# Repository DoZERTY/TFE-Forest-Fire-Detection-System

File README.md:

# ForestFireDetection
This repository contains the work and source files associated with the Master's thesis of Dorian Schrobiltgen. The project builds upon the previous work conducted in [ForestMEv2-public](https://forge.uclouvain.be/nbrusselmans/forestmev2-public).

## Objective

The aim of this thesis is to design and evaluate a low-power, wireless sensor node capable of detecting the early signs of forest fires. The system combines gas sensing, RF communication and optimized embedded hardware/software to ensure early and reliable detection in forest environments, while minimizing the environmental impact of each end-node.

## Project Structure
The repository is devided into four main parts:
### Hardware
- **new_prototype/**: Contains PCB designs, schematics, and Bill of Material (BoM) for the new hardware prototype.
- **test_antenna/**: Designs and schematics related to PCBs used for antenna impedance testing.

### Measurements
- **Gas_sensor/**: Includes raw data, analysis script and plots related to $CO_2$ concentration profile testing.

- **Power_consumption/**: Detailed power consumption for the initial and new prototype.

- **RF_network/**: Results from RF performance tests performed using the antenna impedance testing PCBs

### Simulations
- **Analysis/**: A collection of Python scripts for power consumption modeling, supercapacitor sizing, and generation of plots used in the thesis report.
- **FWI/**: Contains the optimized C implementation of the Fire Weather Index (FWI), along with a repository (by Reid Sawtell in [pyFWI](https://github.com/buckinha/pyfwi)) used for validation.
- **LCA/**: Life Cycle Assessment files used to quantify the environmental impact of each end-node.

### Software
This directory contains the full STM32 projects used to program the boards. Each folder includes all necessary files to build, flash, and debug the corresponding prototype using **STM32CubeIDE**.
- **initial_prototype/**: Complete project and source code of the optimized software for the initial hardware prototype.
- **new_prototype/**: Complete project and source code of the optimized software for the new hardware prototype.

## Author
Dorian Schrobiltgen is an Electrical Engineering student, specializing in Electronics and Power Systems (UCLouvain).

E-mail : dorian.schrobilgen@gmail.com

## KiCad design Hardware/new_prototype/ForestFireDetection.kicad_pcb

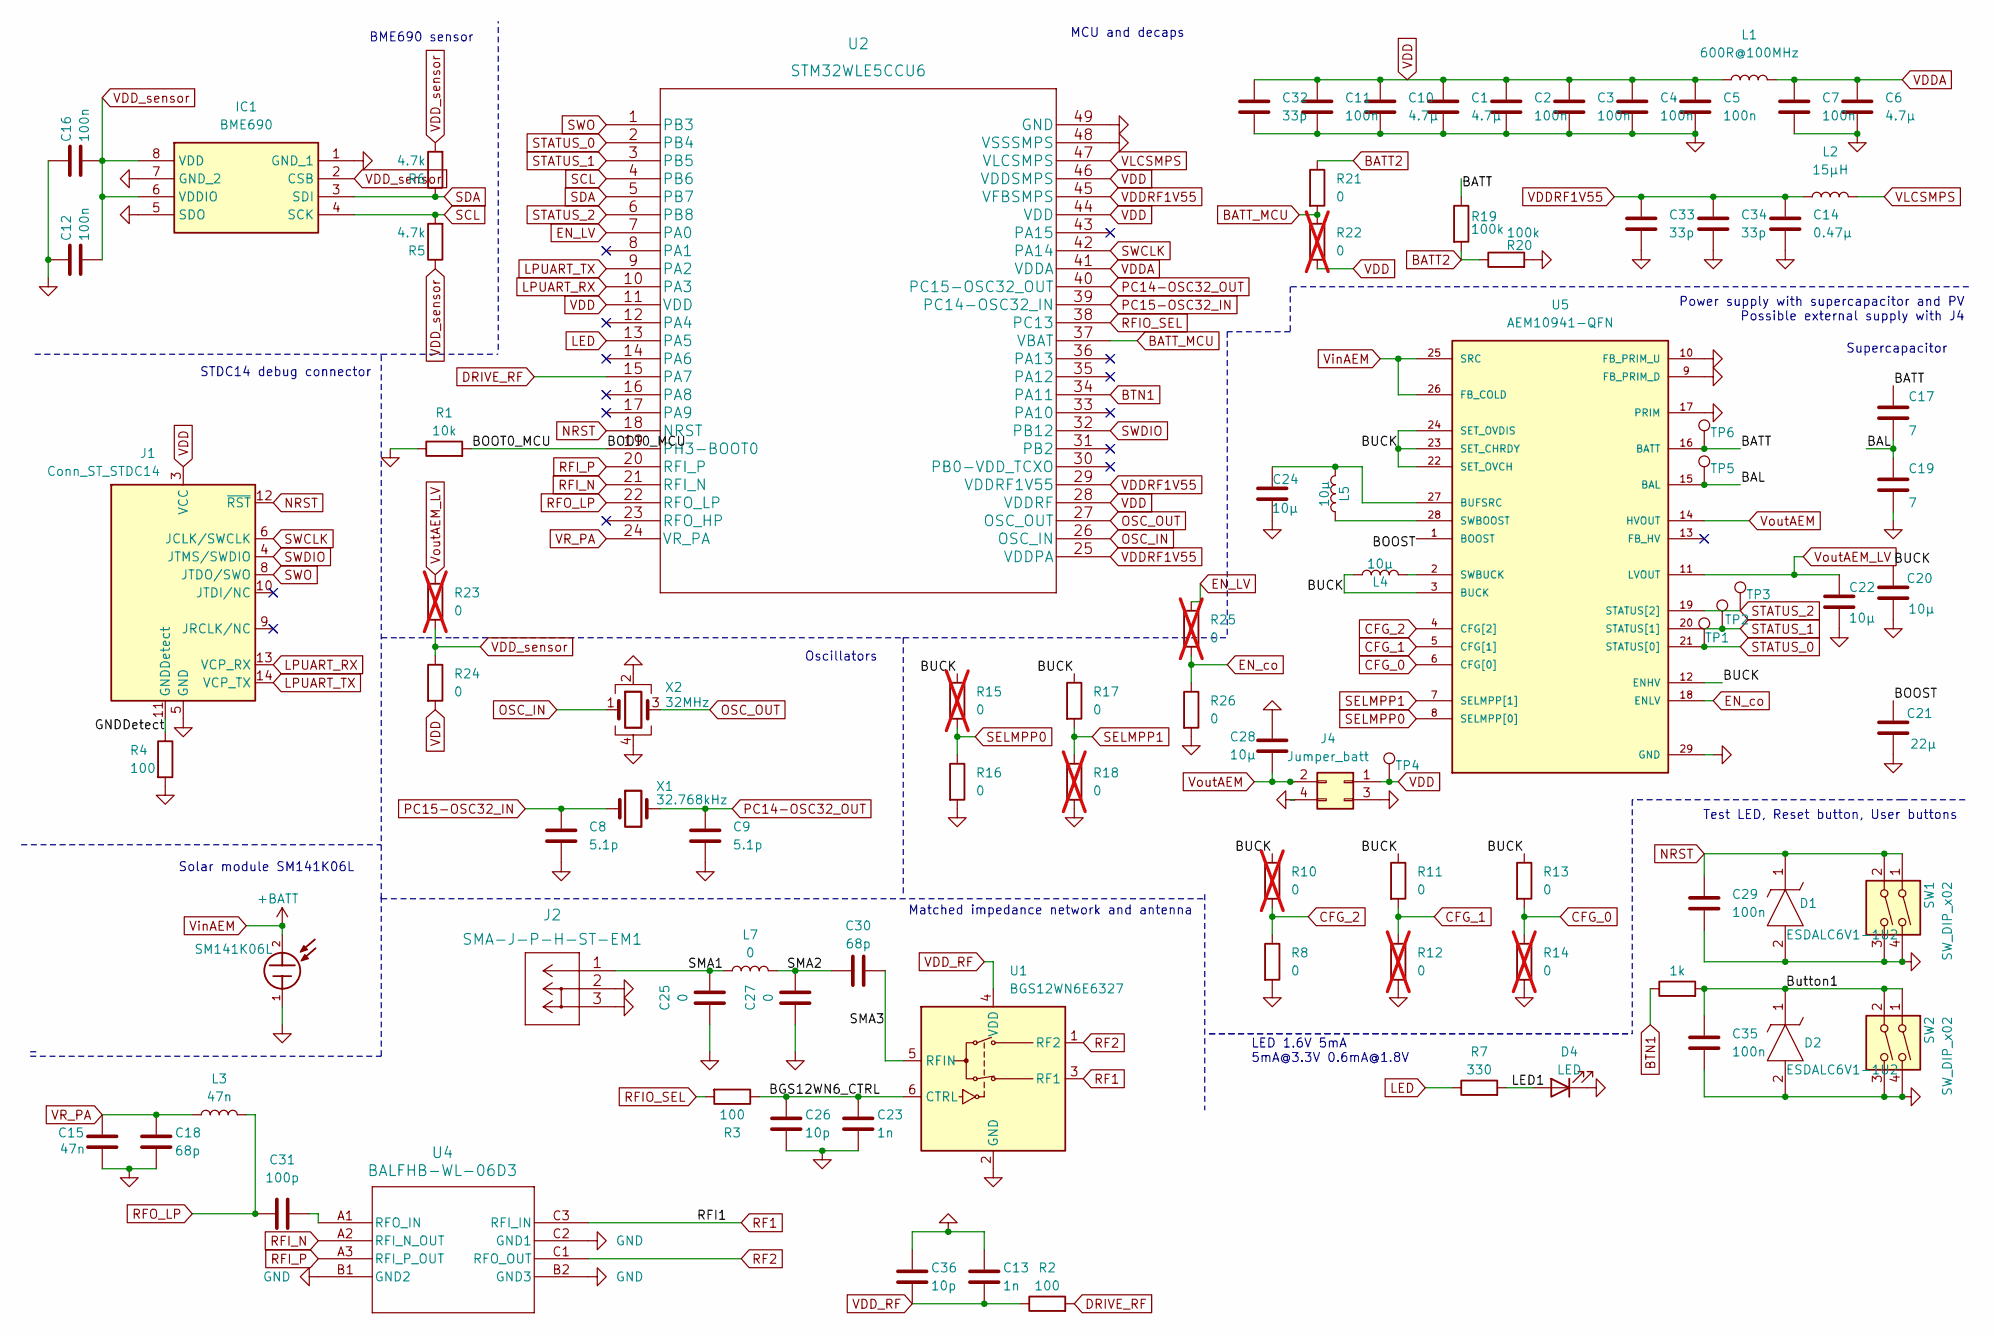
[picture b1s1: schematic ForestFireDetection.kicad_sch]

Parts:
BT1: SM141K06L; PinHeader_1x02_P2.54mm_Vertical; PARTREV August 2023
C1, C6, C10: 4.7µ; C_0402_1005Metric_Pad0.74x0.62mm_HandSolder; Manufacturer_Part_Number GRM155R60J475ME47D
C2, C3, C4, C5, C7, C11, C12, C16, C29, C35: 100n; C_0402_1005Metric_Pad0.74x0.62mm_HandSolder; Manufacturer_Part_Number GRM155R61H104KE19D
C8, C9: 5.1p; C_0402_1005Metric_Pad0.74x0.62mm_HandSolder; Manufacturer_Part_Number GJM1555C1H5R1WB01D
C13, C23: 1n; C_0402_1005Metric_Pad0.74x0.62mm_HandSolder; Manufacturer_Part_Number GRM1555C1H102JA01D
C14: 0.47µ; C_0402_1005Metric_Pad0.74x0.62mm_HandSolder; Manufacturer_Part_Number C1005X5R1E474K050BE
C15: 47n; C_0402_1005Metric_Pad0.74x0.62mm_HandSolder; Manufacturer_Part_Number GRM155C71H473KE19D
C17, C19: 7; C_Disc_D7.5mm_W2.5mm_P5.00mm; Manufacturer_Part_Number MAL222051012E3
C18, C30: 68p; C_0402_1005Metric_Pad0.74x0.62mm_HandSolder; Manufacturer_Part_Number GRM1555C1E680JA01D
C20, C22, C24, C28: 10µ; C_0402_1005Metric_Pad0.74x0.62mm_HandSolder; Manufacturer_Part_Number GRM32DR71E106KA12K
C21: 22µ; C_0402_1005Metric_Pad0.74x0.62mm_HandSolder; Manufacturer_Part_Number GRM155R60G226ME11D
C25, C27: 0; C_0402_1005Metric_Pad0.74x0.62mm_HandSolder
C26, C36: 10p; C_0402_1005Metric_Pad0.74x0.62mm_HandSolder; Manufacturer_Part_Number 04025A100JAT2A
C31: 100p; C_0402_1005Metric_Pad0.74x0.62mm_HandSolder; Manufacturer_Part_Number 04026C101KAT2A
C32, C33, C34: 33p; C_0402_1005Metric_Pad0.74x0.62mm_HandSolder; Manufacturer_Part_Number 04025A330JAT2A
D1, D2: ESDALC6V1-1U2; DIODE_ESDALC6V1-1U2; Mouser Part Number 511-ESDALC6V1-1U2
D4: LED; LED_0402_1005Metric_Pad0.77x0.64mm_HandSolder; Manufacturer_Part_Number 5988A10107F
IC1: BME690; Mouser Part Number 262-BME690
J1: Conn_ST_STDC14; Manufacturer_Part_Number FTSH-107-01-L-DV-K-A
J2: SMA-J-P-H-ST-EM1; CONN_SMA-J-P-H-ST-EM1_SAI; Manufacturer_Part_Number SMA-J-P-H-ST-EM1
J4: Jumper_batt; PinHeader_2x02_P2.54mm_Vertical; Manufacturer_Part_Number 90131-0122
L1: 600R@100MHz; L_0603_1608Metric_Pad1.05x0.95mm_HandSolder; Manufacturer_Part_Number BLM18AG601SN1D
L2: 15µH; L_0805_2012Metric_Pad1.05x1.20mm_HandSolder; Manufacturer_Part_Number LQM21DN150M70L
L3: 47n; L_0402_1005Metric_Pad0.77x0.64mm_HandSolder; Manufacturer_Part_Number LQW15AN47NG00D
L4, L5: 10µ; L_0603_1608Metric_Pad1.05x0.95mm_HandSolder; Manufacturer_Part_Number DFE201210U-1R5M=P2
L7: 0; L_0402_1005Metric_Pad0.77x0.64mm_HandSolder; Manufacturer_Part_Number CRCW06030000Z0EI
R1: 10k; R_0402_1005Metric_Pad0.72x0.64mm_HandSolder; Manufacturer_Part_Number RC0402FR-7D10KL
R2, R3, R4: 100; R_0402_1005Metric_Pad0.72x0.64mm_HandSolder; Manufacturer_Part_Number RC0402FR-7D100RL
R5, R6: 4.7k; R_0402_1005Metric_Pad0.72x0.64mm_HandSolder; Manufacturer_Part_Number RC0402FR-7D4K7L
R7: 330; R_0402_1005Metric_Pad0.72x0.64mm_HandSolder; Manufacturer_Part_Number RC0402JR-7D330RL
R8, R11, R13, R16, R17, R21, R24, R26: 0; R_0603_1608Metric_Pad0.98x0.95mm_HandSolder; Manufacturer_Part_Number CRCW06030000Z0EI
R9: 1k; R_0402_1005Metric_Pad0.72x0.64mm_HandSolder; Manufacturer_Part_Number RC0402FR-7D1KL
R10, R12, R14, R15, R18, R22, R23, R25: 0; R_0603_1608Metric_Pad0.98x0.95mm_HandSolder; not fitted
R19, R20: 100k; R_0402_1005Metric_Pad0.72x0.64mm_HandSolder; Manufacturer_Part_Number RC0402FR-10100KL
SW1, SW2: SW_DIP_x02; SW_B3F-1000_OMR; Manufacturer_Part_Number B3F-1020
TP1, TP2, TP3, TP4, TP5, TP6: TestPoint; TestPoint_Pad_D1.5mm
U1: BGS12WN6E6327; Infineon_PG-TSNP-6-10_0.7x1.1mm_0.7x1.1mm_P0.4mm; Manufacturer_Part_Number BGS12WN6E6327XTSA1
U2: STM32WLE5CCU6; Manufacturer_Part_Number STM32WLE5CCU6
U4: BALFHB-WL-06D3; CSPG8_1P83X2P13_STM; Manufacturer_Part_Number BALFHB-WL-06D3
U5: AEM10941-QFN; QFN50P500X500X90-29N; PARTREV 1.4
X1: 32.768kHz; Crystal_SMD_2012-2Pin_2.0x1.2mm; Manufacturer_Part_Number NX2012SA-32.768K-STD-MUB-1
X2: 32MHz; Crystal_SMD_2016-4Pin_2.0x1.6mm; Manufacturer_Part_Number CX2016SA32000F0FZZG4

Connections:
/BAL: C17.2, C19.1, TP5.1, U5.15 (BAL)
/BATT: C17.1, R19.1, TP6.1, U5.16 (BATT)
/BGS12WN6_CTRL: C23.1, C26.1, R3.1, U1.6 (CTRL)
/BOOST: C21.1, U5.1 (BOOST)
/BOOT0_MCU: R1.2, U2.19 (PH3-BOOT0)
/BUCK: C20.1, L4.1, R10.1, R11.1, R13.1, R15.1, R17.1, U5.3 (BUCK), U5.12 (ENHV), U5.22 (SET_OVCH), U5.23 (SET_CHRDY), U5.24 (SET_OVDIS)
/Button1: C35.1, D2.1, R9.2, SW2.1, SW2.2
/GNDDetect: J1.11 (GNDDetect), R4.1
/LED1: D4.2 (A), R7.2
/SMA1: C25.2, J2.1, L7.1
/SMA2: C27.2, C30.1, L7.2
/SMA3: C30.2, U1.5 (RFIN)
BATT2: R19.2, R20.1, R21.1
BATT_MCU: R21.2, R22.1, U2.37 (VBAT)
BTN1: R9.1, U2.34 (PA11)
CFG_0: R13.2, R14.1, U5.6 (CFG[0])
CFG_1: R11.2, R12.1, U5.5 (CFG[1])
CFG_2: R8.1, R10.2, U5.4 (CFG[2])
DRIVE_RF: R2.2, U2.15 (PA7)
EN_LV: R25.1, U2.7 (PA0)
EN_co: R25.2, R26.1, U5.18 (ENLV)
GND: BT1.1, C1.2, C2.2, C3.2, C4.2, C5.2, C6.2, C7.2, C8.2, C9.2, C10.2, C11.2, C12.1, C13.1, C14.2, C15.2, C16.1, C18.2, C19.2, C20.2, C21.2, C22.2, C23.2, C24.2, C25.1, C26.2, C27.1, C28.1, C29.2, C32.2, C33.2, C34.2, C35.2, C36.1, D1.2, D2.2, D4.1 (K), IC1.1 (GND_1), IC1.5 (SDO), IC1.7 (GND_2), J1.5 (GND), J1.7 (GND), J2.2, J2.3, J4.3, J4.4, R1.1, R4.2, R8.2, R12.2, R14.2, R16.2, R18.2, R20.2, R26.2, SW1.3, SW1.4, SW2.3, SW2.4, U1.2 (GND), U2.48 (VSSSMPS), U2.49 (GND), U4.B1 (GND2), U4.B2 (GND3), U4.C2 (GND1), U5.9 (FB_PRIM_D), U5.10 (FB_PRIM_U), U5.17 (PRIM), U5.29 (GND), X2.2, X2.4
LED: R7.1, U2.13 (PA5)
LPUART_RX: J1.13 (VCP_RX), U2.10 (PA3)
LPUART_TX: J1.14 (VCP_TX), U2.9 (PA2)
NRST: C29.1, D1.1, J1.12 (~RST), SW1.1, SW1.2, U2.18 (NRST)
unnamed: C31.2, U4.A1 (RFO_IN)
unnamed: C24.1, L5.2, U5.27 (BUFSRC)
unnamed: L5.1, U5.28 (SWBOOST)
unnamed: L4.2, U5.2 (SWBUCK)
OSC_IN: U2.26 (OSC_IN), X2.1
OSC_OUT: U2.27 (OSC_OUT), X2.3
PC14-OSC32_OUT: C9.1, U2.40 (PC15-OSC32_OUT), X1.2
PC15-OSC32_IN: C8.1, U2.39 (PC14-OSC32_IN), X1.1
RF1: U1.3 (RF1), U4.C3 (RFI_IN)
RF2: U1.1 (RF2), U4.C1 (RFO_OUT)
RFIO_SEL: R3.2, U2.38 (PC13)
RFI_N: U2.21 (RFI_N), U4.A2 (RFI_N_OUT)
RFI_P: U2.20 (RFI_P), U4.A3 (RFI_P_OUT)
RFO_LP: C31.1, L3.2, U2.22 (RFO_LP)
SCL: IC1.4 (SCK), R5.2, U2.4 (PB6)
SDA: IC1.3 (SDI), R6.1, U2.5 (PB7)
SELMPP0: R15.2, R16.1, U5.8 (SELMPP[0])
SELMPP1: R17.2, R18.1, U5.7 (SELMPP[1])
STATUS_0: TP1.1, U2.2 (PB4), U5.21 (STATUS[0])
STATUS_1: TP2.1, U2.3 (PB5), U5.20 (STATUS[1])
STATUS_2: TP3.1, U2.6 (PB8), U5.19 (STATUS[2])
SWCLK: J1.6 (JCLK/SWCLK), U2.42 (PA14)
SWDIO: J1.4 (JTMS/SWDIO), U2.32 (PB12)
SWO: J1.8 (JTDO/SWO), U2.1 (PB3)
VDD: C1.1, C2.1, C3.1, C4.1, C5.1, C10.1, C11.1, C32.1, J1.3 (VCC), J4.1, L1.1, R22.2, R24.2, TP4.1, U2.11 (VDD), U2.28 (VDDRF), U2.44 (VDD), U2.46 (VDDSMPS)
VDDA: C6.1, C7.1, L1.2, U2.41 (VDDA)
VDDRF1V55: C14.1, C33.1, C34.1, L2.1, U2.25 (VDDPA), U2.29 (VDDRF1V55), U2.45 (VFBSMPS)
VDD_RF: C13.2, C36.2, R2.1, U1.4 (VDD)
VDD_sensor: C12.2, C16.2, IC1.2 (CSB), IC1.6 (VDDIO), IC1.8 (VDD), R5.1, R6.2, R23.2, R24.1
VLCSMPS: L2.2, U2.47 (VLCSMPS)
VR_PA: C15.1, C18.1, L3.1, U2.24 (VR_PA)
VinAEM: BT1.2, U5.25 (SRC), U5.26 (FB_COLD)
VoutAEM: C28.2, J4.2, U5.14 (HVOUT)
VoutAEM_LV: C22.1, R23.1, U5.11 (LVOUT)

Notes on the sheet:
STDC14 debug connector
MCU and decaps
Solar module SM141K06L
Supercapacitor
LED 1.6V 5mA 5mA@3.3V 0.6mA@1.8V
BME690 sensor
Matched impedance network and antenna
Oscillators
Test LED, Reset button, User buttons
Power supply with supercapacitor and PV Possible external supply with J4

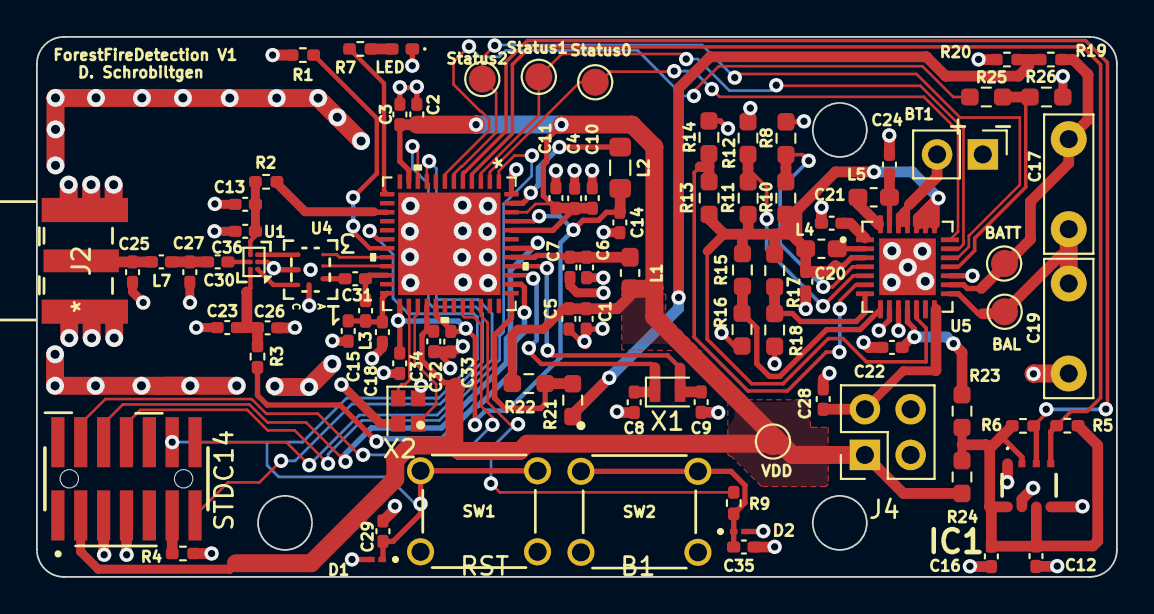
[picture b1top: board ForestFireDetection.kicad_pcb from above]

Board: 2 copper layers, 60.0 x 30.0 mm, 90 parts (0 on the bottom side), 60 nets.

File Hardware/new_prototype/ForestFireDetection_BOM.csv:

;NBr of PCBs:;2;;;;;;
;Provider:;Mouser Electronics;;;;;;
;;;;;;;;
;;;;;;;;
Reference;Value;Unit cost [];Qty per PCB;Qty to order;Total cost [];Manufacturer_Name;Manufacturer_Part_Number;Manufacturer_Reference_Mouser
C1,C6,C10;4.7µ;0.105;3;6;0.63;Murata Electronics; GRM155R60J475ME47D;81-GRM155R60J475ME7D
C2,C3,C4,C5,C7,C11,C12,C16,C29,C35;100n;0.095;10;20;1.9;Murata Electronics;GRM155R61H104KE19D;81-GRM155R61H104KE9D
C8,C9;5.1p;0.152;2;4;0.608;Murata Electronics;GJM1555C1H5R1WB01D;81-GJM1555C1H5R1WB1D
C13,C23;1n;0.095;2;4;0.38;Murata Electronics; GRM1555C1H102JA01D;81-GRM1555C1H102JA1D
C14;0.47µ;0.124;1;2;0.248;TDK;C1005X5R1E474K050BE;810-C1005X5R1E474KE
C15;47n;0.095;1;2;0.19;Murata Electronics;GRM155C71H473KE19D;81-GRM155C71H473KE9D
C17,C19;7;3.3;2;4;13.2;Vishay / BC Components;MAL222051012E3;594-MAL222051012E3
C18,C30;68p;0.095;2;4;0.38;Murata Electronics;GRM1555C1E680JA01D;81-GRM1555C1E680JA1D
C20,C22,C24,C28;10µ;0.779;4;8;6.232;Murata Electronics;GRM32DR71E106KA12K;81-GRM32DR71E106KA2K
C21;22µ;0.238;1;2;0.476;Murata Electronics;GRM155R60G226ME11D;81-GRM155R60G226ME1D
L7,R8,R11,R13,R16,R17,R21;0;0.095;7;14;1.33;Vishay / Dale;CRCW06030000Z0EI;71-CRCW06030000Z0EI
C26,C36;10p;0.095;2;4;0.38;KYOCERA AVX;04025A100JAT2A;581-04025A100J
C31;100p;0.2;1;2;0.4;KYOCERA AVX;04026C101KAT2A;581-04026C101KAT2A
C32,C33,C34;33p;0.095;3;6;0.57;KYOCERA AVX;04025A330JAT2A;581-04025A330J
D1,D2;ESDALC6V1-1U2;0.238;2;4;0.952;STMicroelectronics;ESDALC6V1-1U2;511-ESDALC6V1-1U2
D4;LED;0.266;1;2;0.532; Dialight;5988A10107F;645-5988A10107F
IC1;BME690;7.86;1;2;15.72;BOSCH;BME690;262-BME690
J1;Conn_ST_STDC14;3.05;1;2;6.1;Samtec;FTSH-107-01-L-DV-K-A;200-FTSH10701LDVKA
J2;SMA-J-P-H-ST-EM1;2.52;1;2;5.04; Samtec; SMA-J-P-H-ST-EM1;200-SMAJPHSTEM1
J4;Jumper_batt;0.447;1;2;0.894;Molex;90131-0122;538-90131-0122
L1;600R@100MHz;0.095;1;2;0.19;Murata Electronics;BLM18AG601SN1D;81-BLM11A601S
L2;15µ;0.19;1;2;0.38;Murata Electronics; LQM21DN150M70L;81-LQM21DN150M70L
L3;47n;0.105;1;2;0.21;Murata Electronics; LQW15AN47NG00D;81-LQW15AN47NG00D
L4,L5;10µ;0.2;2;4;0.8;Murata Electronics;LQM21DH100M70L;81-LQM21DH100M70L
R1;10k;0.095;1;2;0.19;YAGEO; RC0402FR-7D10KL;603-RC0402FR-7D10KL
R2,R3,R4;100;0.095;3;6;0.57;YAGEO;RC0402FR-7D100RL;603-RC0402FR-7D100RL
R5,R6;4.7k;0.095;2;4;0.38;YAGEO;RC0402FR-7D4K7L;603-RC0402FR-7D4K7L
R7;330;0.095;1;2;0.19;YAGEO;RC0402JR-7D330RL;603-RC0402JR-7D330RL
R9;1k;0.095;1;2;0.19;YAGEO;RC0402FR-7D1KL;603-RC0402FR-7D1KL
R19,R20;100k;0.095;2;4;0.38;YAGEO;RC0402FR-10100KL;603-RC0402FR-10100KL
SW1,SW2;SW_DIP_x02;0.285;2;4;1.14;Omron;B3F-1020;653-B3F-1020
U1;BGS12WN6E6327;0.314;1;3;0.942; Infineon;BGS12WN6E6327XTSA1;726-BGS12WN6E6327XTS
U2;STM32WLE5CCU6;6.75;1;2;13.5; STMicroelectronics; STM32WLE5CCU6;511-STM32WLE5CCU6
U4;BALFHB-WL-06D3;0.76;3;6;4.56;STMicroelectronics; BALFHB-WL-06D3;511-BALFHB-WL-06D3
U5;AEM10941-QFN;4.19;1;2;8.38;e-peas;AEM10941-QFN;120-AEM10941-QFN
X1;32.768kHz;0.808;1;2;1.616;NDK;NX2012SA-32.768K-STD-MUB-1;344-NX2012SA32768K1
X2;32MHz;0.684;1;2;1.368;KYOCERA AVX;CX2016SA32000F0FZZG4;581-CX2016SA32FFZZG4
;Resistor 0;0.095;1;2;0.19;Vishay / Dale;CRCW06030000Z0EI;71-CRCW06030000Z0EI
 ;Antenna;5.18;1;2;10.36;Taoglas;TI.08.C.0111;960-TI.08.C.0111
;SMA-J-P-H-ST-EM1;2.52;2;4;10.08; Samtec; SMA-J-P-H-ST-EM1;200-SMAJPHSTEM1
;Header 2pins 2.54;0.96;1;2;1.92;Hirose Connector;HIF3GA-2.54SP;798-HIF3GA-2.54SP
;;;;;;;;
;;;;Total:;113.698;;;

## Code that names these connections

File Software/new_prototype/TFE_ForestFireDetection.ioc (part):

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Mcu.Name=STM32WLE5CCUx
Mcu.Package=UFQFPN48
Mcu.UserName=STM32WLE5CCUx
PA0.GPIOParameters=GPIO_Label
PA0.GPIO_Label=EN_LV
PA0.Signal=GPIO_Output
PA1.Signal=GPIO_Analog
PA10.Signal=GPIO_Analog
PA11.GPIOParameters=GPIO_PuPd,GPIO_Label
PA11.GPIO_Label=BTN1
PA11.GPIO_PuPd=GPIO_PULLUP
PA11.Signal=GPXTI11
PA12.Signal=GPIO_Analog
PA13.Mode=Serial_Wire
PA13.Signal=DEBUG_JTMS-SWDIO
PA14.Mode=Serial_Wire
PA14.Signal=DEBUG_JTCK-SWCLK
PA15.Signal=GPIO_Analog
PA2.Mode=Asynchronous
PA2.Signal=LPUART1_TX
PA3.Mode=Asynchronous
PA3.Signal=LPUART1_RX
PA5.GPIOParameters=GPIO_Label
PA5.GPIO_Label=LED
PA5.Signal=GPIO_Output
PA6.Signal=GPIO_Analog
PA7.GPIOParameters=GPIO_Label
PA7.GPIO_Label=DRIVE_RF_Pin
PA7.Signal=GPIO_Output
PA8.Signal=GPIO_Analog
PA9.Signal=GPIO_Analog
PB12.GPIOParameters=GPIO_Label
PB12.GPIO_Label=DO_NOT_USE
PB12.Signal=GPIO_Input
PB2.Signal=GPIO_Analog
PB4.Signal=GPIO_Analog
PB5.Signal=GPIO_Analog
PB6.Mode=I2C
PB6.Signal=I2C1_SCL
PB7.Mode=I2C
PB7.Signal=I2C1_SDA
PB8.Signal=GPIO_Analog
PC14-OSC32_IN.Mode=LSE-External-Oscillator
PC14-OSC32_IN.Signal=RCC_OSC32_IN
PC15-OSC32_OUT.Mode=LSE-External-Oscillator
PC15-OSC32_OUT.Signal=RCC_OSC32_OUT
PH3-BOOT0.Signal=GPIO_Analog
RCC.HSE_VALUE=32000000
RCC.SYSCLKFreq_VALUE=400000
board=custom

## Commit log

2026-05-30 Add files
2026-05-30 Add thesis report
2026-05-30 Update README
    Added author information and corrected formatting issues.

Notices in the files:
parts and their libraries:
Copyright 2021 Accelerated Designs. All rights reserved.
